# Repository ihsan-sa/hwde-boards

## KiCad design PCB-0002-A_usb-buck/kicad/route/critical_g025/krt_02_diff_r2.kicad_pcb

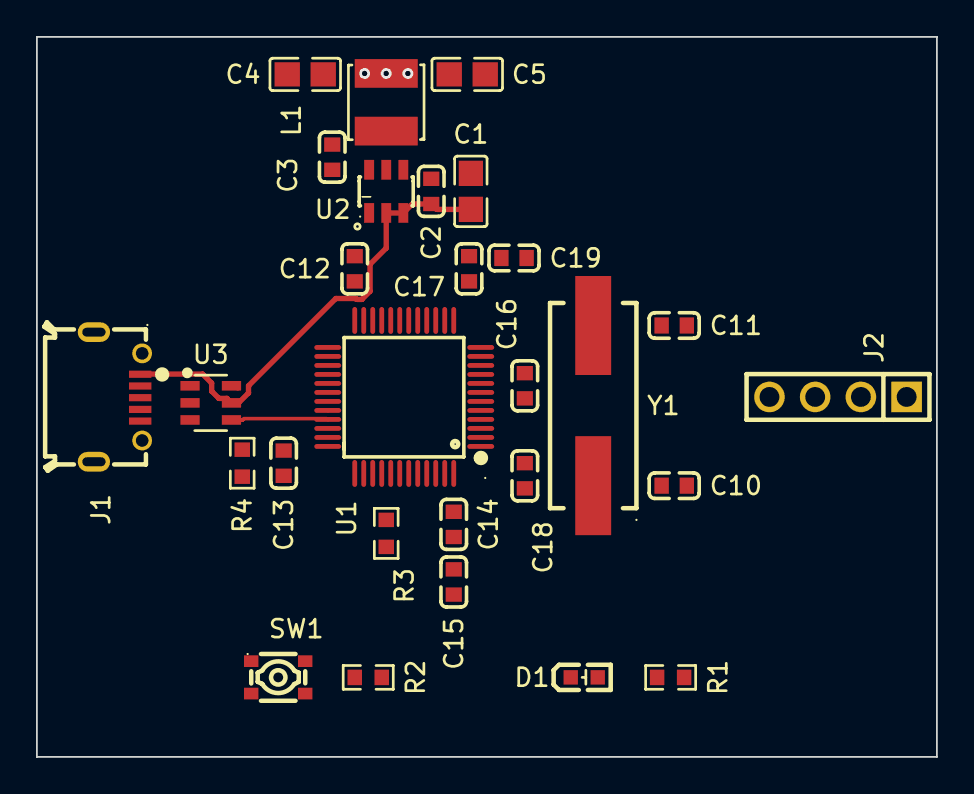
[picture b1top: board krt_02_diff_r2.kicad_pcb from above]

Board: 4 copper layers, 50.0 x 40.0 mm, 28 parts (0 on the bottom side), 16 nets.

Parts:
C1: 10uF 25V X5R; C0805
C2, C3, C12, C13, C14, C16, C18, C19: 100nF 50V X7R; C0603
C4, C5: 22uF 25V X5R; C0805
C10, C11: 22pF 50V C0G; C0603
C15: 4.7uF 16V X5R; C0603
C17: 1uF 50V X5R; C0603
D1: Red 0603; LED-SMD_L1.6-W0.8-R-RD
J1: USB Micro-B receptacle SMD; USB-SMD_USB-111FD-B-SU
J2: 1x4 2.54mm male THT; HDR-TH_4P-P2.54-V-M
L1: 4.7uH; IND-SMD_L4.0-W4.0
R1: 1k; R0603
R2, R3: 10k; R0603
R4: 1.5k; R0603
SW1: SMD tactile switch; SW-SMD_4P-L3.0-W2.6-P1.80-LS3.4-TL
U1: STM32F103C8T6; LQFP-48_L7.0-W7.0-P0.50-LS9.0-BL
U2: AP63203QWU-7; TSOT-26_L2.9-W1.6-P0.95-LS2.8-BL
U3: USBLC6-2SC6; SOT-23-6_L2.9-W1.6-P0.95-LS2.8-BL
Y1: 8MHz 20pF; CRYSTAL-SMD_L11.5-W4.8-LS12.7

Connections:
+3V3: C4.1, C5.1, C12.1, C13.1, C14.1, C15.1, C16.1, C17.1, C18.1, J2.1, L1.2, R1.2, R2.2, R4.2, U1.1, U1.9, U1.24, U1.36, U1.48, U2.1
/USB_DM: J1.2, U1.32, U3.1, U3.6
/USB_DP: J1.3, U1.33, U3.3, U3.4
/mcu/BOOT0: R3.1, U1.44
/mcu/BTN: R2.1, SW1.1, SW1.2, U1.18
/mcu/LED: D1.2, U1.2
/mcu/LED_A: D1.1, R1.1
/mcu/NRST: C19.1, U1.7
/mcu/OSC_IN: C10.1, U1.5, Y1.1
/mcu/OSC_OUT: C11.1, U1.6, Y1.2
/mcu/SWCLK: J2.2, U1.37
/mcu/SWDIO: J2.4, U1.34
/power/BST: C3.1, U2.6
/power/SW: C3.2, L1.1, U2.5
GND: C1.2, C2.2, C4.2, C5.2, C10.2, C11.2, C12.2, C13.2, C14.2, C15.2, C16.2, C17.2, C18.2, C19.2, J1.5, J1.6, J1.7, J1.8, J1.9, J2.3, R3.2, SW1.3, SW1.4, U1.8, U1.23, U1.35, U1.47, U2.4, U3.2
VBUS: C1.1, C2.1, J1.1, U2.2, U2.3, U3.5

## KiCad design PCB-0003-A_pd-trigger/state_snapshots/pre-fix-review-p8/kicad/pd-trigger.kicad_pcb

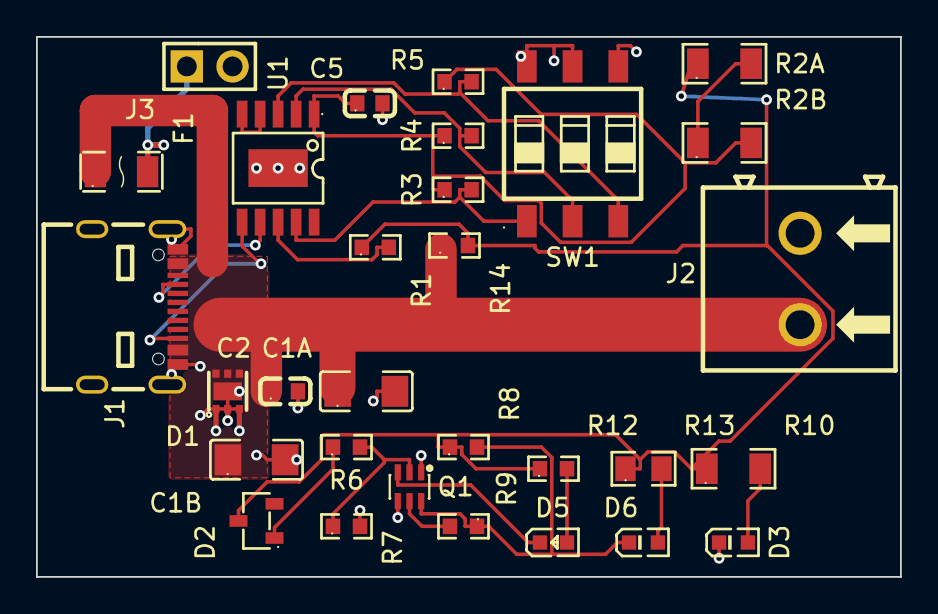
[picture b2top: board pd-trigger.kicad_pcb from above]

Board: 2 copper layers, 48.0 x 30.0 mm, 30 parts (0 on the bottom side), 21 nets.

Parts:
C1A, C1B: 10uF 50V X5R; C1206
C2: 100nF 50V X7R; C0603
C5: 1uF 50V X5R; C0603
D1: TVS2200 22V; WSON-6_L2.0-W2.0-P0.65-BL-EP
D2: BZX84C6V2; SOT-23-3_L2.9-W1.3-P1.90-LS2.4-BR
D3: LED YG PWR; LED0603-RD_GREEN
D5: LED RED 5V ONLY; LED0603-RD
D6: LED YG PROFILE OK; LED0603-RD_GREEN
F1: PPTC 1A 30V; F1206
J1: USB-C 16P 5A; USB-C-SMD_MC-311D
J2: SCREW 5.08 2P; CONN-TH_P5.08_KF128-5.08-2P
J3: HDR 1x2 AUX; HDR-TH_2P-P2.54-V-M-3
Q1: BC847BS; SOT-363-6_L2.2-W1.3-P0.65-LS2.1-BL
R1, R8: 10k; R0603
R2A, R2B: 510R; R1206
R3, R4, R5: 100k; R0603
R6: 6.8k; R0603
R7: 4.7k; R0603
R9: 47k; R0603
R10: 3.3k; R1206
R12: 1.5k; R0603
R13: 4.7k; R0805
R14: 0R; R0603
SW1: DIP-3; SW-SMD_6P-L7.6-W6.0-P2.54-LS9.3-BL
U1: CH224K; ESSOP-10_L4.9-W3.9-P1.0-LS6.0-TL-EP

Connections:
/BC12_DIS: U1.4, U1.5
/CC1: J1.A5, U1.7
/CC2: J1.B5, U1.6
/CFG1: R3.2, SW1.1, U1.9
/CFG2: R4.2, SW1.2, U1.2
/CFG3: R5.2, SW1.3, U1.3
/D3_A: D3.2, R10.2
/D5_A: D5.2, R12.2
/D6_A: D6.2, R13.2
/FB_B: Q1.5, R9.2
/FB_K: D5.1, Q1.3
/HV_B: Q1.2, R6.2, R7.1
/HV_OK: D6.1, Q1.6, R8.2, R9.1
/R2_MID: R2A.2, R2B.1
/VAUX: F1.2, J3.1
/VDD: C5.1, R2B.2, R3.1, R4.1, R5.1, U1.1
/VIND: D2.3, R1.1, R2A.1, R8.1, R10.1, R12.1, R13.1, R14.2
/VSENSE: R1.2, U1.8
/ZBIAS: D2.1, R6.1
GND: C1A.2, C1B.2, C2.2, C5.2, D1.1, D1.2, D1.3, D1.7, D3.1, J1.1, J1.2, J1.3, J1.4, J1.A1-B12, J1.B1-A12, J2.2, J3.2, Q1.1, Q1.4, R7.2, SW1.4, SW1.5, SW1.6, U1.11
VBUS: C1A.1, C1B.1, C2.1, D1.4, D1.5, D1.6, F1.1, J1.A4-B9, J1.B4-A9, J2.1, R14.1
